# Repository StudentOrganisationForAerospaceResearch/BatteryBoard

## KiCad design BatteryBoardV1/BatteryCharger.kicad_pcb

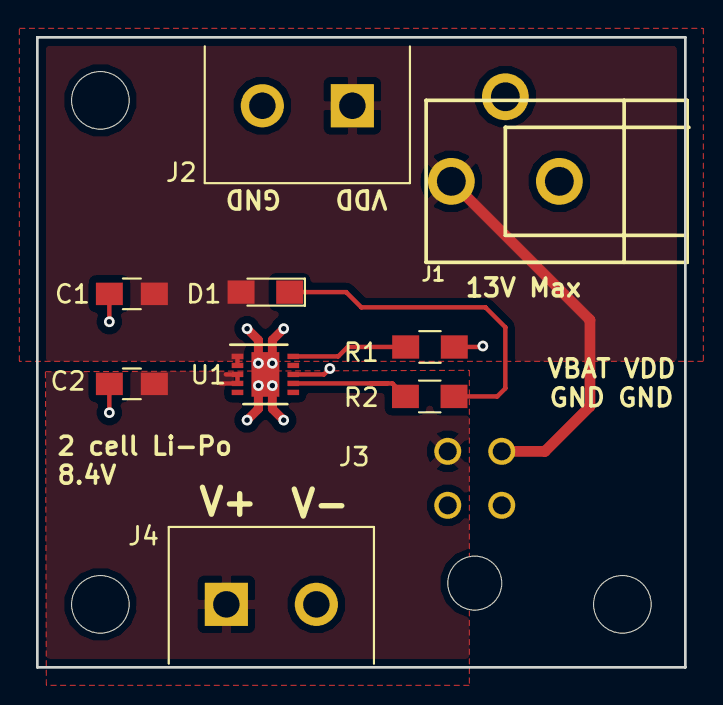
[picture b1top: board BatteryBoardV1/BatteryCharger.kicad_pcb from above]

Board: 2 copper layers, 36.0 x 35.0 mm, 14 parts (1 on the bottom side), 6 nets.

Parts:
C1, C2: 4.7u; C_0805_HandSoldering
D1: LED; LED_0805_HandSoldering
J1: Barrel_Jack; CUI_PJ-102A_2.5mm_DC_JACK
J2: Input Terms.; TerminalBlock_5mm_2POS_ED2600
J3: Conn_01x04_Male; Molex_Micro-Fit_3.0_43045-0400_2x02_P3.00mm_Horizontal
J4: Bat.Terms.; TerminalBlock_5mm_2POS_ED2600
LOGO_SOAR: LOGO_SOAR
MK1, MK2, MK3: Mounting_Hole; MountingHole_3.2mm_M3
R1: 3K; R_0805_HandSoldering
R2: 1K; R_0805_HandSoldering
U1: MCP73213; DFN-10-1EP_3x3mm_Pitch0.5mm

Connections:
/VBAT+: C2.1, J3.4, J4.1, U1.3, U1.4
GND: C1.2, C2.2, J1.2, J1.3, J2.2, J3.1, J3.2, J4.2, R1.2, U1.8, U1.11
unnamed: D1.1, R2.2
unnamed: R1.1, U1.10
unnamed: R2.1, U1.7
VDD: C1.1, D1.2, J1.1, J2.1, J3.3, U1.1, U1.2

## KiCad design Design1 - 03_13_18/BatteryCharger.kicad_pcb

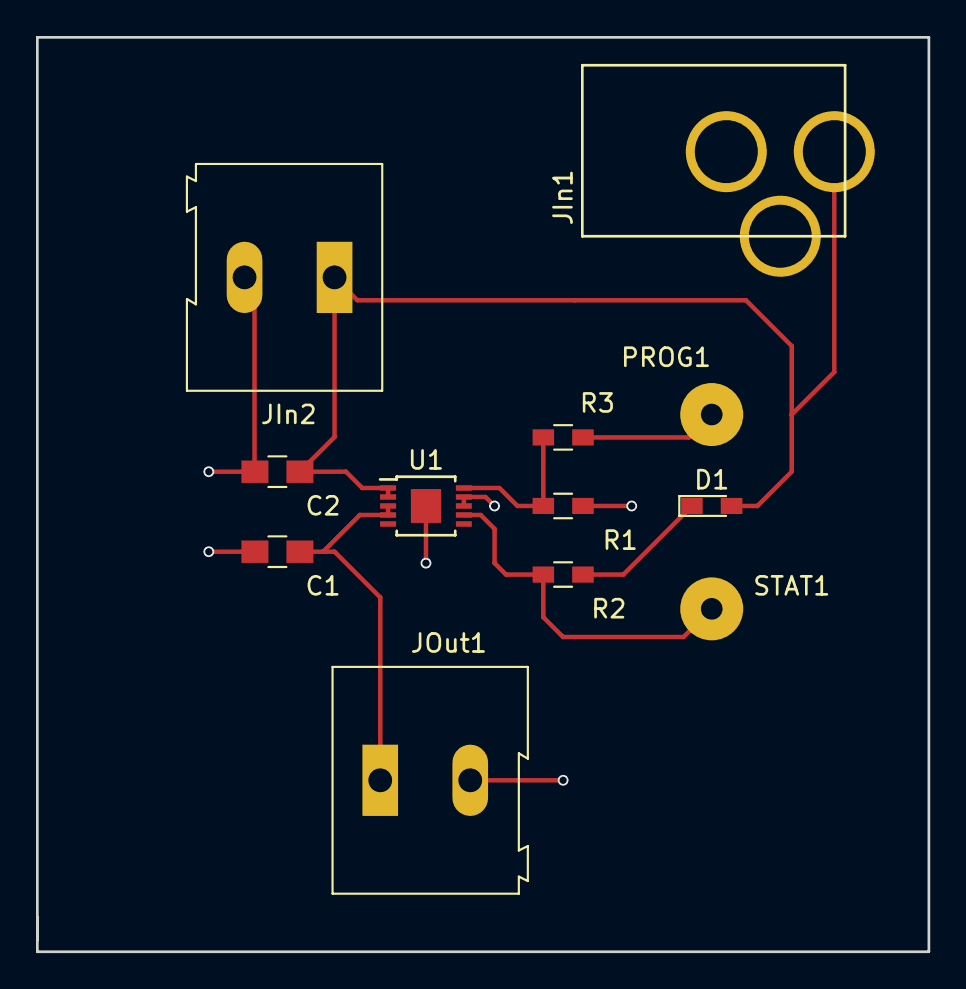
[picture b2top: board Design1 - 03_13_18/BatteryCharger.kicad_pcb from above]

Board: 2 copper layers, 49.5 x 50.8 mm, 12 parts (0 on the bottom side), 7 nets.

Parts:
C1, C2: 4.7u; C_0805_HandSoldering
D1: LED; LED_0603_HandSoldering
JIn1: Barrel_Jack; DC_2.1mm_CUI-PJ-202A
JIn2: Input Terms.; TerminalBlock_Altech_AK300-2_P5.00mm
JOut1: Bat.Terms.; TerminalBlock_Altech_AK300-2_P5.00mm
PROG1: TP5; SolderWirePad_single_1-2mmDrill
R1, R3: 2.37K; R_0603_HandSoldering
R2: 1K; R_0603_HandSoldering
STAT1: TP6; SolderWirePad_single_1-2mmDrill
U1: MCP73213; MSOP-10-1EP_3x3mm_Pitch0.5mm

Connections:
GND: C1.2, C2.2, JIn1.2, JIn1.3, JIn2.2, JOut1.2, R1.2, U1.8, U1.9, U1.11
unnamed: C1.1, JOut1.1, U1.3, U1.4
unnamed: D1.1, R2.2
unnamed: PROG1.1, R3.2
unnamed: R1.1, R3.1, U1.10
unnamed: R2.1, STAT1.1, U1.7
VDD: C2.1, D1.2, JIn1.1, JIn2.1, U1.1, U1.2

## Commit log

2018-04-20 Rename Design2 - 03_17_18/BatCharge.bak to BatteryBoardV1/BatCharge.bak
2018-05-05 remove fp-lib-table. Prevent library incompatibility
2018-05-05 Rearrange components to add mounting holes and silkscreen
2018-05-17 final design published. Gerbers and schematic PDF generated.
